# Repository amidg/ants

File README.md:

# ANTS Robotics
Capstone project for Simon Fraser University Summer 2021 cohort.\
Developed by the following guys:
- [Ibrahim Helal - Autonomy and Self-Driving](https://www.ihelal.com/pac)
- [Dmitrii Gusev - Embedded](https://www.linkedin.com/in/dmitriigusev/)
- [James Z Liu - Mechanical](https://www.linkedin.com/in/jameszliu/)
- [Nam Mai - Teleoperation](https://www.linkedin.com/in/nam-anh-mai/)

## Project Goal:
Develop state-of-the-art mobile robotics platfrom (AGV) targeting manufacturing businesses. Robot's electronic hardware must provide direct path for linear scalability from smaller systems all the way to the bigger robots. Same functionality modules can be stacked together on the ITX-style carrier board allowing to increase robot's capabilities.

## Repo structure:
Firmware:
- LED Controller
- Drive Control Unit (DCU)
- Power Control Unit (PCU)

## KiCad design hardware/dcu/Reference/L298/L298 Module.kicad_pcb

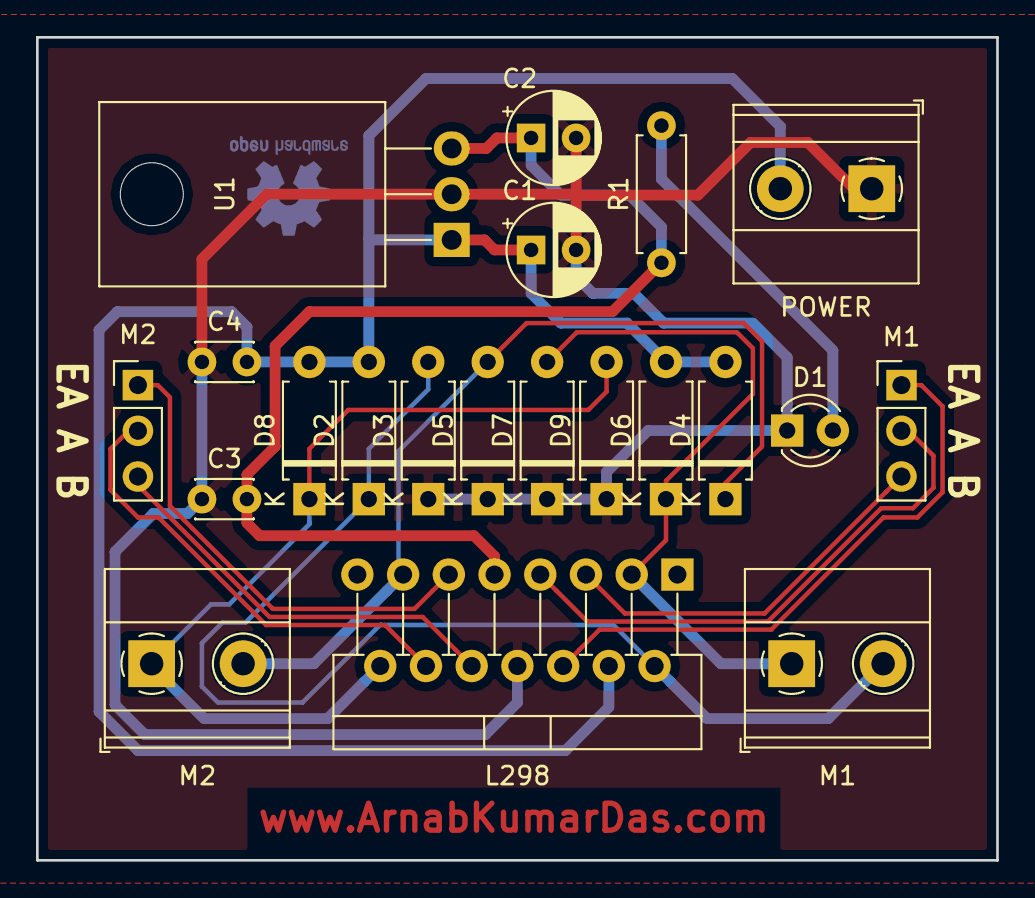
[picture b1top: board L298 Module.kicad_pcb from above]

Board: 2 copper layers, 53.3 x 45.7 mm, 21 parts (0 on the bottom side), 14 nets.

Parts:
C1, C2: 47u; CP_Radial_D5.0mm_P2.50mm
C3, C4: 100n; C_Disc_D3.0mm_W2.0mm_P2.50mm
D1: LED; LED_D3.0mm
D2, D3, D4, D5, D6, D7, D8, D9: 1N4007; D_A-405_P7.62mm_Horizontal
L298: L298HN; TO-220-15_P2.54x2.54mm_StaggerOdd_Lead4.58mm_Vertical
M1: MOTOR1 IN; PinHeader_1x03_P2.54mm_Vertical
M1#2: MOTOR1 OUT; TerminalBlock_Phoenix_MKDS-1,5-2-5.08_1x02_P5.08mm_Horizont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
M2: MOTOR2 IN; PinHeader_1x03_P2.54mm_Vertical
M2#2: MOTOR2 OUT; TerminalBlock_Phoenix_MKDS-1,5-2-5.08_1x02_P5.08mm_Horizont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
POWER: POWER; TerminalBlock_Phoenix_MKDS-1,5-2-5.08_1x02_P5.08mm_Horizont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
R1: R; R_Axial_DIN0207_L6.3mm_D2.5mm_P7.62mm_Horizontal
U1: L7805; TO-220-3_Horizontal_TabDown

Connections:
+5V: C2.1, C3.2, L298.9, R1.1, U1.3
+BATT: C1.1, C4.2, D2.2, D4.2, D6.2, D8.2, L298.4, POWER.2, U1.1
GND: C1.2, C2.2, C3.1, C4.1, D1.1, D3.1, D5.1, D7.1, D9.1, L298.8, POWER.1, U1.2
unnamed: D1.2, R1.2
unnamed: D2.1, D3.2, L298.2, M1#2.2
unnamed: D4.1, D5.2, L298.13, M2#2.2
unnamed: D6.1, D7.2, L298.3, M1#2.1
unnamed: D8.1, D9.2, L298.14, M2#2.1
unnamed: L298.6, M1.1
unnamed: L298.7, M1.2
unnamed: L298.5, M1.3
unnamed: L298.11, M2.1
unnamed: L298.12, M2.2
unnamed: L298.10, M2.3

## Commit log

2025-01-03 readme
2025-01-03 firmware added from 2021
2025-01-03 added architecture files
2025-01-03 18650 balancer board
2025-01-03 base board
2025-01-03 motor board
